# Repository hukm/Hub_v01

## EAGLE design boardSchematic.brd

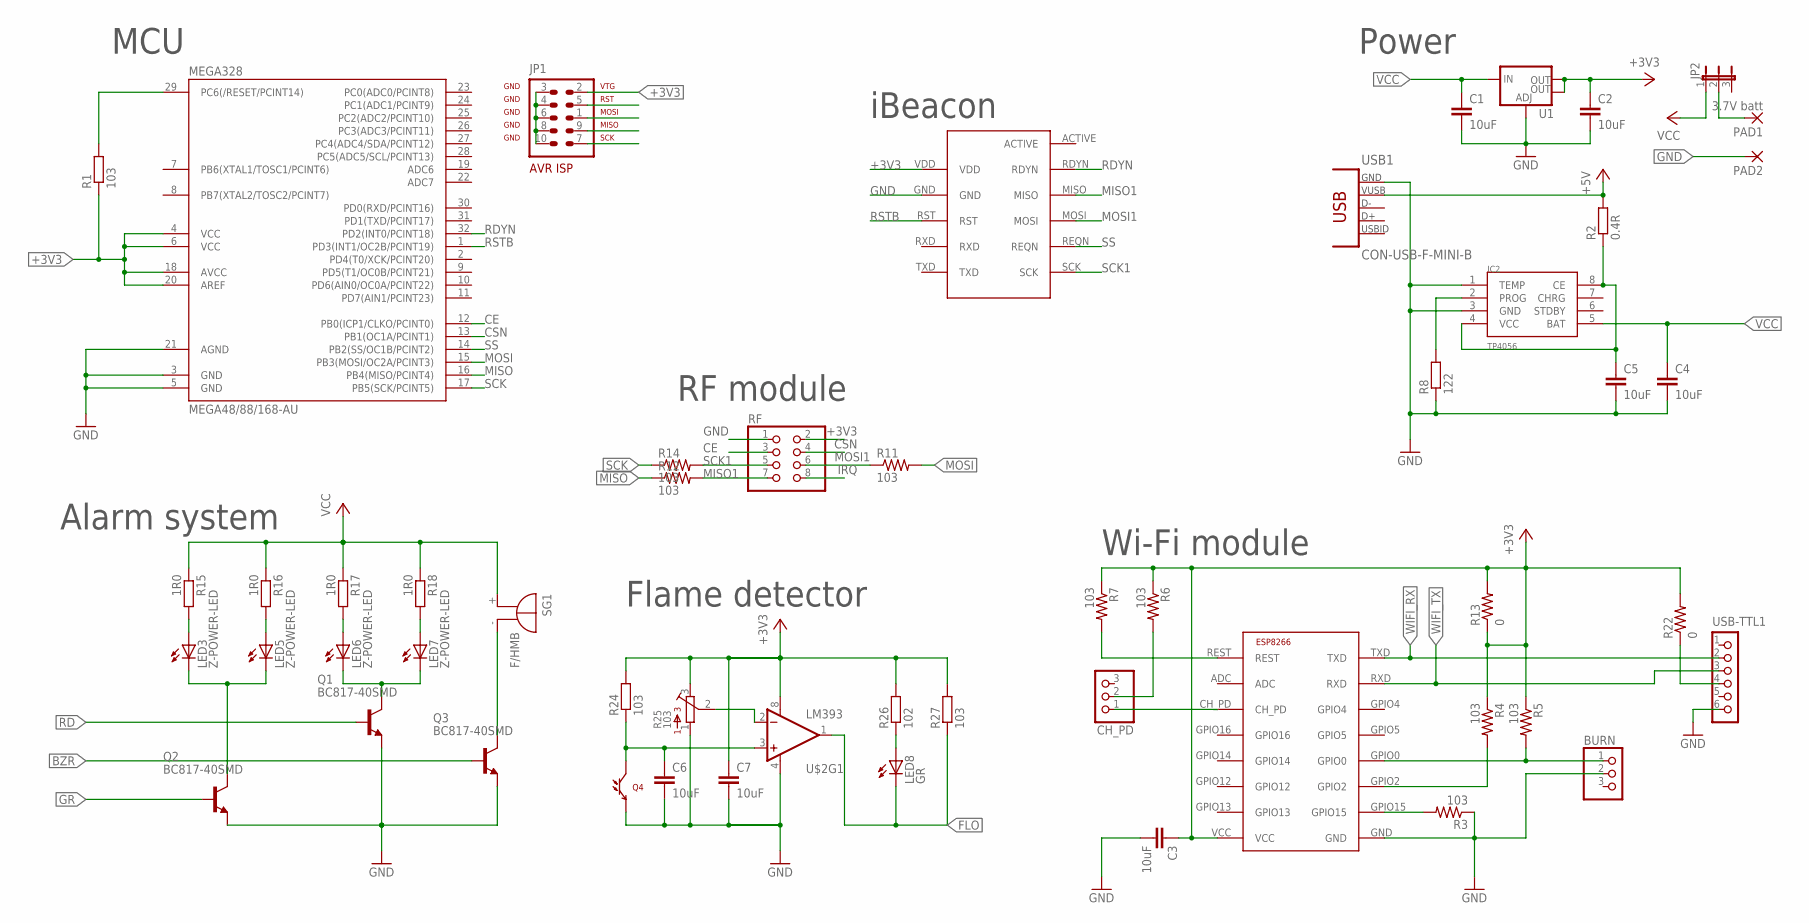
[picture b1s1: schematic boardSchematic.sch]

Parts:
BEACON: MOD-NRF8001MOD-NRF8001; MOD-NRF8001
BURN: PINHD-1X3; 1X03
C1, C2, C3, C6, C7: 10uF; C0805
C4, C5: 10uF; C1210
CH_PD: PINHD-1X3; 1X03
IC2: TP4056; SOP-8
JP1: AVR-ISP-10
JP2: JP2E; JP2
LED3, LED5, LED6, LED7: Z-POWER-LED; Z-POWER-LED-PCB-TYPE
LED8: GR; SML0805
MEGA328: MEGA48/88/168-AU; TQFP32-08
PAD1: 3.7V batt; SMD2,54-5,08
PAD2: SMD5; SMD2,54-5,08
Q1, Q2, Q3: BC817-40SMD; SOT23-BEC
Q4: LTR-301
R1, R3, R4, R5, R6, R7, R11, R12, R14, R24, R27: 103; R0805
R2: 0.4R; R1210W
R8: 122; R0805
R13, R22: 0; R1206
R15, R16, R17, R18: 1R0; R1206
R25: 103; 3362P
R26: 102; R0805
RF: PINHD-2X4; 2X04
SG1: F/HMB
U1: V_REG_LM1117SOT223; SOT223
U$1: ESP8266; ESP-03
U$2: LM393; SO08
USB1: CON-USB-F-MINI-B; CONN_USB_MINI-B
USB-TTL1: CON_HEADER_1X06-SMD-RIGHT-ANGLED; M1X6_MALE_RIGHT_ANGLED_SMD

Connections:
+3V3: BEACON.VDD, C2.1, C3.1, C7.1, JP1.2, MEGA328.4 (VCC), MEGA328.6 (VCC), MEGA328.18 (AVCC), MEGA328.20 (AREF), R1.1, R4.1, R5.1, R6.1, R7.1, R13.1, R13.2, R22.2, R24.2, R25.3, R26.2, R27.2, RF.2, U1.2 (OUT), U1.4 (OUT), U$1.VCC, U$2.8 (V+)
+5V: R2.2, USB1.VUSB
BZR: Q3.B
CE: MEGA328.12 (PB0(ICP1/CLKO/PCINT0)), RF.3
CSN: MEGA328.13 (PB1(OC1A/PCINT1)), RF.4
FLO: LED8.C, R27.1, U$2.1 (OUT)
GND: BEACON.GND, BURN.2, C1.2, C2.2, C3.2, C4.2, C5.2, C6.2, C7.2, IC2.1 (TEMP), IC2.3 (GND), JP1.3, JP1.4, JP1.6, JP1.8, JP1.10, MEGA328.3 (GND), MEGA328.5 (GND), MEGA328.21 (AGND), PAD2.1, Q1.E, Q2.E, Q3.E, Q4.E, R3.1, R8.1, R25.1, RF.1, U1.1 (ADJ), U$1.GND, U$2.4 (V-), USB1.GND, USB-TTL1.6
GR: Q2.B
IRQ: RF.8
MISO: JP1.9, MEGA328.16 (PB4(MISO/PCINT4)), R12.1
MISO1: BEACON.MISO, R12.2, RF.7
MOSI: JP1.1, MEGA328.15 (PB3(MOSI/OC2A/PCINT3)), R11.2
MOSI1: BEACON.MOSI, R11.1, RF.6
unnamed: CH_PD.1, U$1.CH_PD
unnamed: R3.2, U$1.GPIO15
unnamed: R4.2, U$1.GPIO2
unnamed: BURN.1, R5.2, U$1.GPIO0
unnamed: IC2.2 (PROG), R8.2
unnamed: CH_PD.2, R6.2
unnamed: R7.2, U$1.REST
unnamed: C5.1, IC2.4 (VCC), IC2.8 (CE), R2.1
unnamed: LED3.A, R15.2
unnamed: LED5.A, R16.2
unnamed: LED6.A, R17.2
unnamed: LED7.A, R18.2
unnamed: LED6.C, LED7.C, Q1.C
unnamed: LED3.C, LED5.C, Q2.C
unnamed: C6.1, Q4.C, R24.1, U$2.3 (+IN)
unnamed: Q3.C, SG1.-
unnamed: R25.2, U$2.2 (-IN)
unnamed: LED8.A, R26.1
unnamed: R22.1, USB-TTL1.4
unnamed: JP2.2, PAD1.1
RD: Q1.B
RDYN: BEACON.RDYN, MEGA328.32 (PD2(INT0/PCINT18))
RST: JP1.5, MEGA328.29 (PC6(/RESET/PCINT14)), R1.2
RSTB: BEACON.RST, MEGA328.1 (PD3(INT1/OC2B/PCINT19))
SCK: JP1.7, MEGA328.17 (PB5(SCK/PCINT5)), R14.1
SCK1: BEACON.SCK, R14.2, RF.5
SS: BEACON.REQN, MEGA328.14 (PB2(SS/OC1B/PCINT2))
VCC: C1.1, C4.1, IC2.5 (BAT), JP2.1, R15.1, R16.1, R17.1, R18.1, SG1.+, U1.3 (IN)
WIFI_RX: U$1.TXD, USB-TTL1.2
WIFI_TX: U$1.RXD, USB-TTL1.3

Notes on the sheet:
Wi-Fi module
Flame detector
Alarm system
MCU
iBeacon
RF module
Power

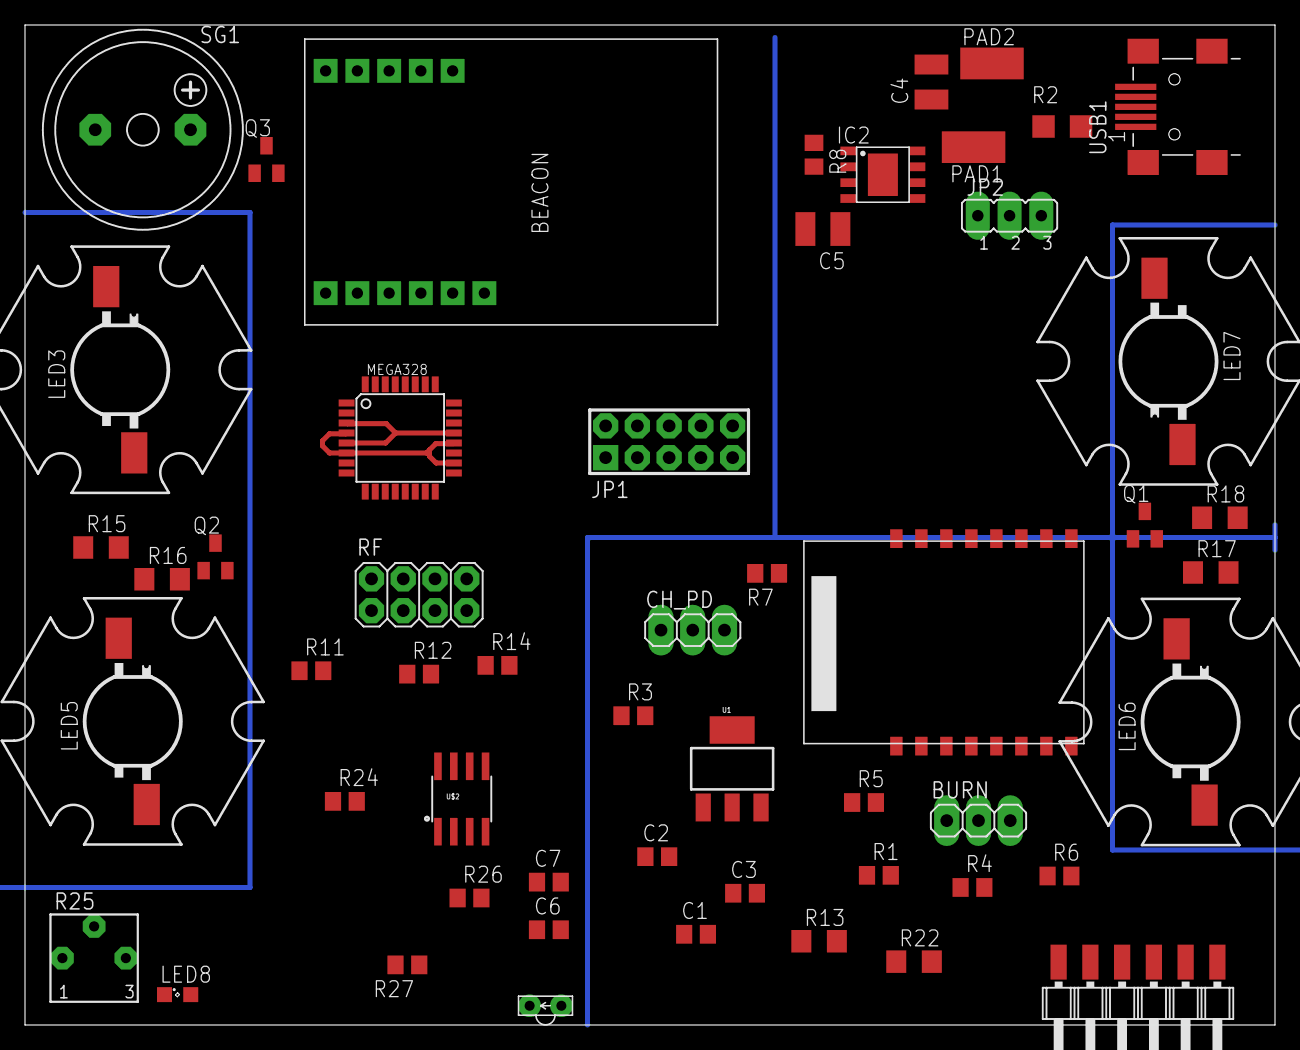
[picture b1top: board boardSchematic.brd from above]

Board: 2 copper layers, 100.0 x 80.0 mm, 55 parts (0 on the bottom side), 39 nets.

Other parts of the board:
U$4: LOCAID_LOGO
U$5: LOCAID_LOGO_BIG

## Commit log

2016-05-19 Added on/off switch
2016-05-19 First guess of routing
2016-05-19 Test 2
2016-05-19 Moved pin header
2016-05-19 Test3
2016-05-19 Test4

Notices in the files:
parts and their libraries:
powerIC: Licensing: Creative Commons ShareAlike 4.0 International - https://creativecommons.org/licenses/by-sa/4.0
